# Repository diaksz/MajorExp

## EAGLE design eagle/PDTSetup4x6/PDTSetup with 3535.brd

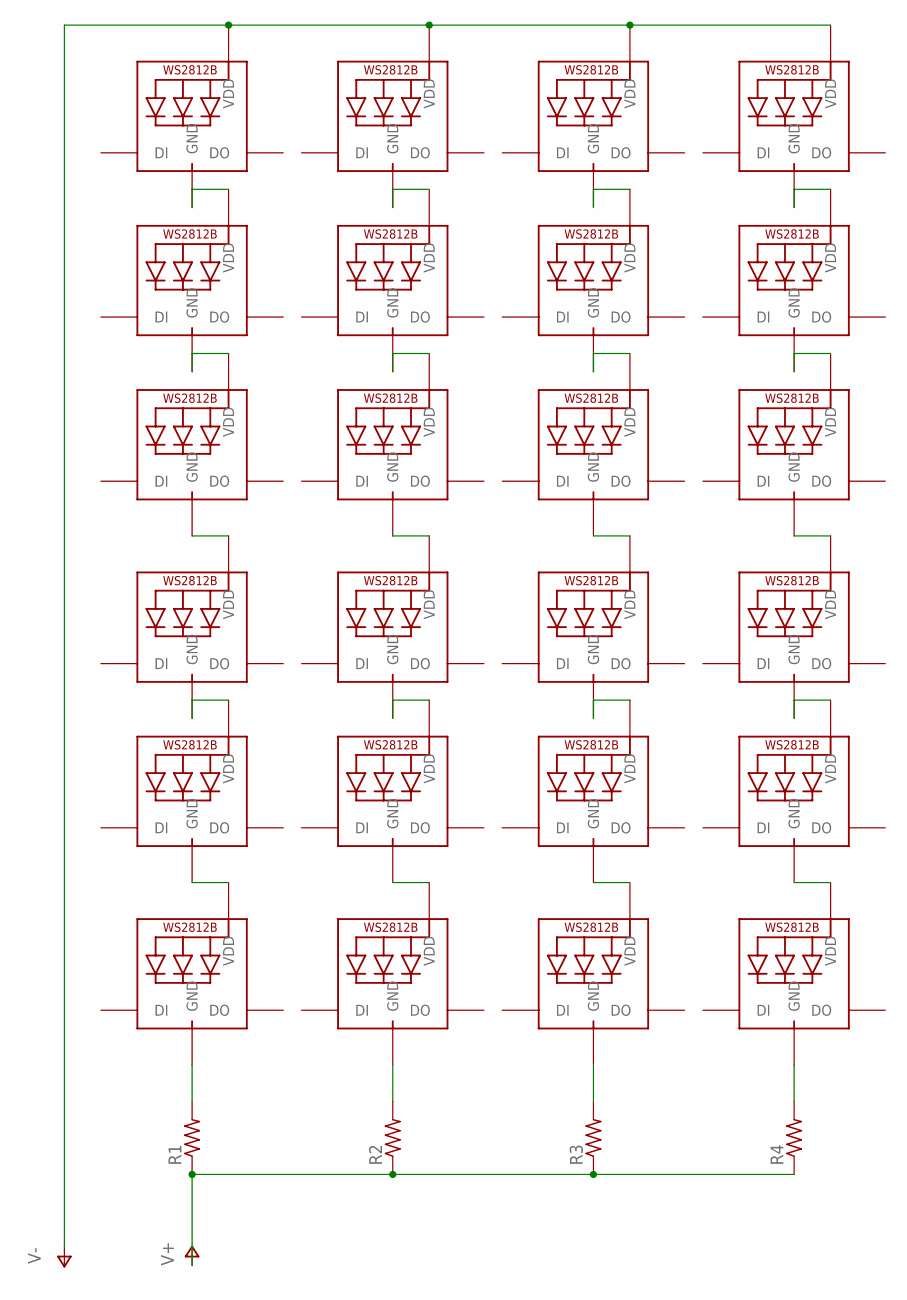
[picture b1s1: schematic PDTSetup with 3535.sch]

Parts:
LED1, LED2, LED3, LED4, LED5, LED6, LED7, LED8, LED9, LED10, LED11, LED12, LED13, LED14, LED15, LED16, LED17, LED18, LED19, LED20, LED21, LED22, LED23, LED24: WS2812B3535; LED3535
R1, R2, R3, R4: R-US_0207/15; 0207/15

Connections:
unnamed: LED24.4 (GND), R4.2
unnamed: LED13.4 (GND), R3.2
unnamed: LED12.4 (GND), R2.2
unnamed: LED6.4 (GND), R1.2
unnamed: LED5.4 (GND), LED6.2 (VDD)
unnamed: LED11.4 (GND), LED12.2 (VDD)
unnamed: LED13.2 (VDD), LED14.4 (GND)
unnamed: LED23.4 (GND), LED24.2 (VDD)
unnamed: LED4.4 (GND), LED5.2 (VDD)
unnamed: LED10.4 (GND), LED11.2 (VDD)
unnamed: LED14.2 (VDD), LED15.4 (GND)
unnamed: LED22.4 (GND), LED23.2 (VDD)
unnamed: LED21.4 (GND), LED22.2 (VDD)
unnamed: LED15.2 (VDD), LED16.4 (GND)
unnamed: LED9.4 (GND), LED10.2 (VDD)
unnamed: LED3.4 (GND), LED4.2 (VDD)
unnamed: LED2.4 (GND), LED3.2 (VDD)
unnamed: LED8.4 (GND), LED9.2 (VDD)
unnamed: LED16.2 (VDD), LED17.4 (GND)
unnamed: LED20.4 (GND), LED21.2 (VDD)
unnamed: LED19.4 (GND), LED20.2 (VDD)
unnamed: LED17.2 (VDD), LED18.4 (GND)
unnamed: LED7.4 (GND), LED8.2 (VDD)
unnamed: LED1.4 (GND), LED2.2 (VDD)
V+: R1.1, R2.1, R3.1, R4.1
V-: LED1.2 (VDD), LED7.2 (VDD), LED18.2 (VDD), LED19.2 (VDD)

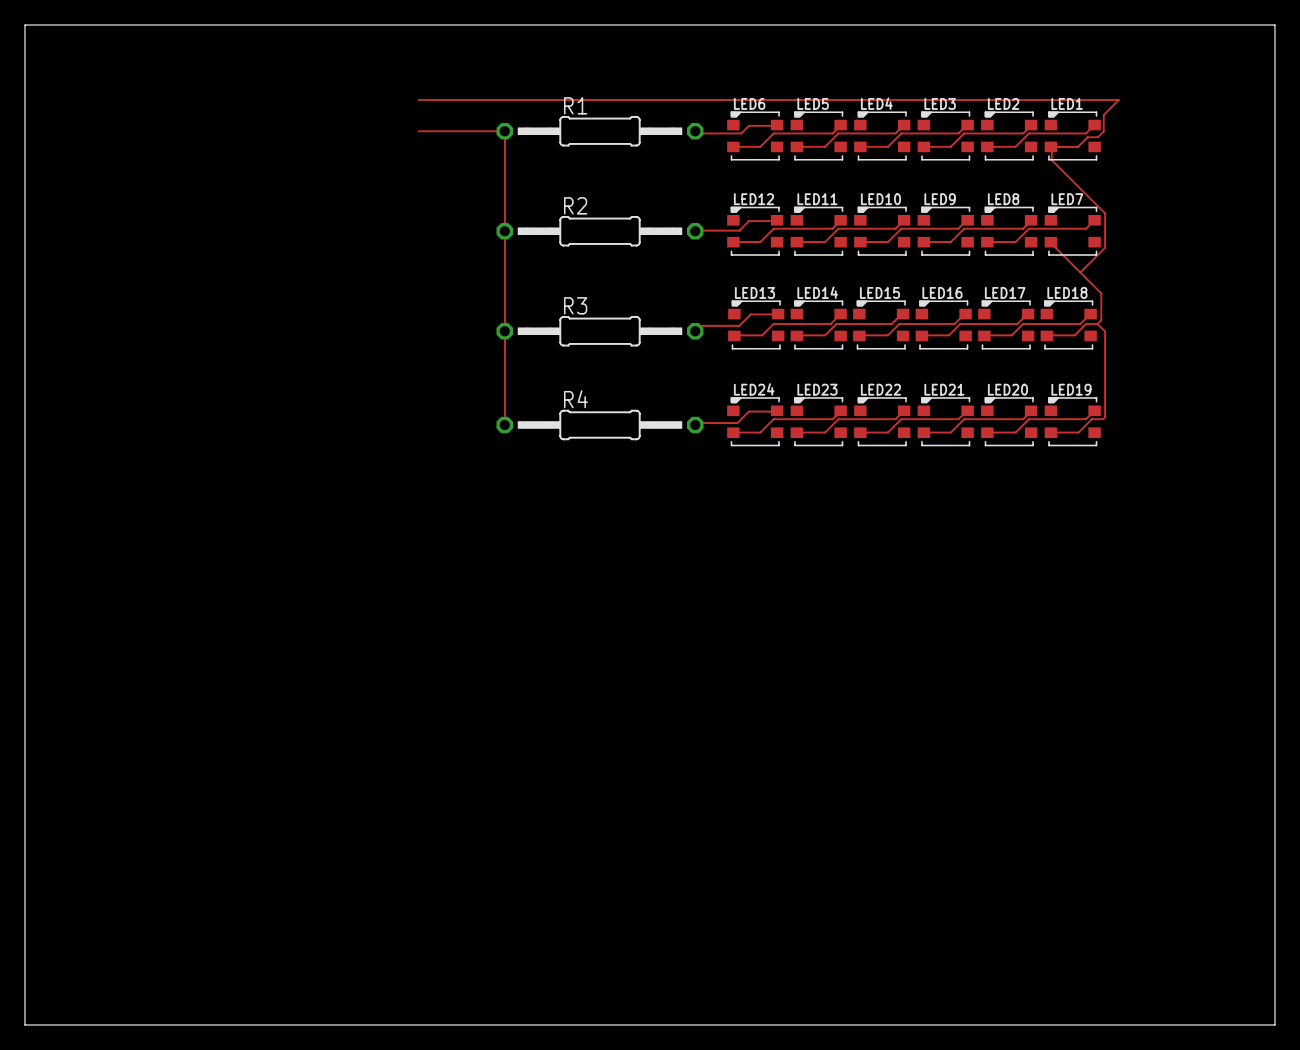
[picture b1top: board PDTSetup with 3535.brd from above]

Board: 2 copper layers, 100.0 x 80.0 mm, 28 parts (0 on the bottom side), 26 nets.

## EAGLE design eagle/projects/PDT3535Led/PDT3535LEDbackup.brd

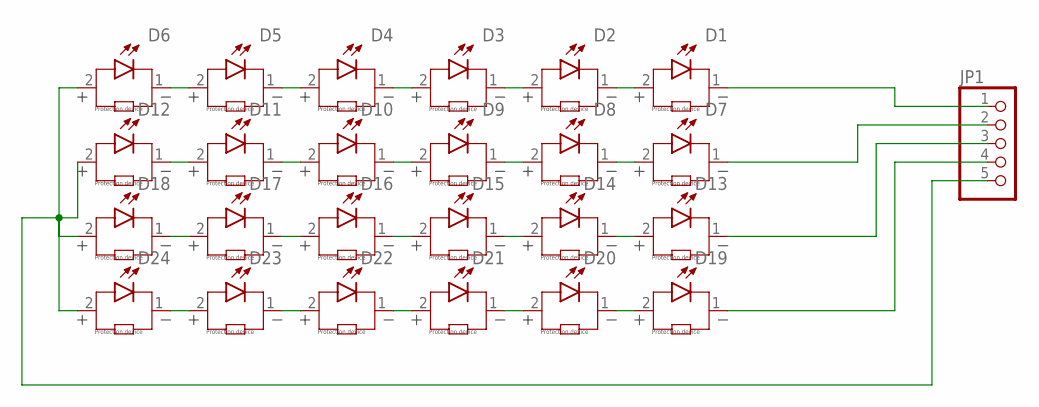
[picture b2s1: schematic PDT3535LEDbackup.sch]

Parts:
D1, D2, D3, D4, D5, D6, D7, D8, D9, D10, D11, D12, D13, D14, D15, D16, D17, D18, D19, D20, D21, D22, D23, D24: WL-SWTC_3535_158353060_6000K; WL-SWTC_3535
JP1: PINHD-1X05_2.54-SMD-90°; 1X05SMD/90

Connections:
unnamed: D6.2, D12.2, D18.2, D24.2, JP1.5
unnamed: D5.2, D6.1
unnamed: D4.2, D5.1
unnamed: D3.2, D4.1
unnamed: D2.2, D3.1
unnamed: D1.2, D2.1
unnamed: D11.2, D12.1
unnamed: D17.2, D18.1
unnamed: D23.2, D24.1
unnamed: D22.2, D23.1
unnamed: D16.2, D17.1
unnamed: D10.2, D11.1
unnamed: D9.2, D10.1
unnamed: D15.2, D16.1
unnamed: D21.2, D22.1
unnamed: D20.2, D21.1
unnamed: D14.2, D15.1
unnamed: D8.2, D9.1
unnamed: D7.2, D8.1
unnamed: D13.2, D14.1
unnamed: D19.2, D20.1
unnamed: D19.1, JP1.4
unnamed: D13.1, JP1.3
unnamed: D7.1, JP1.2
unnamed: D1.1, JP1.1

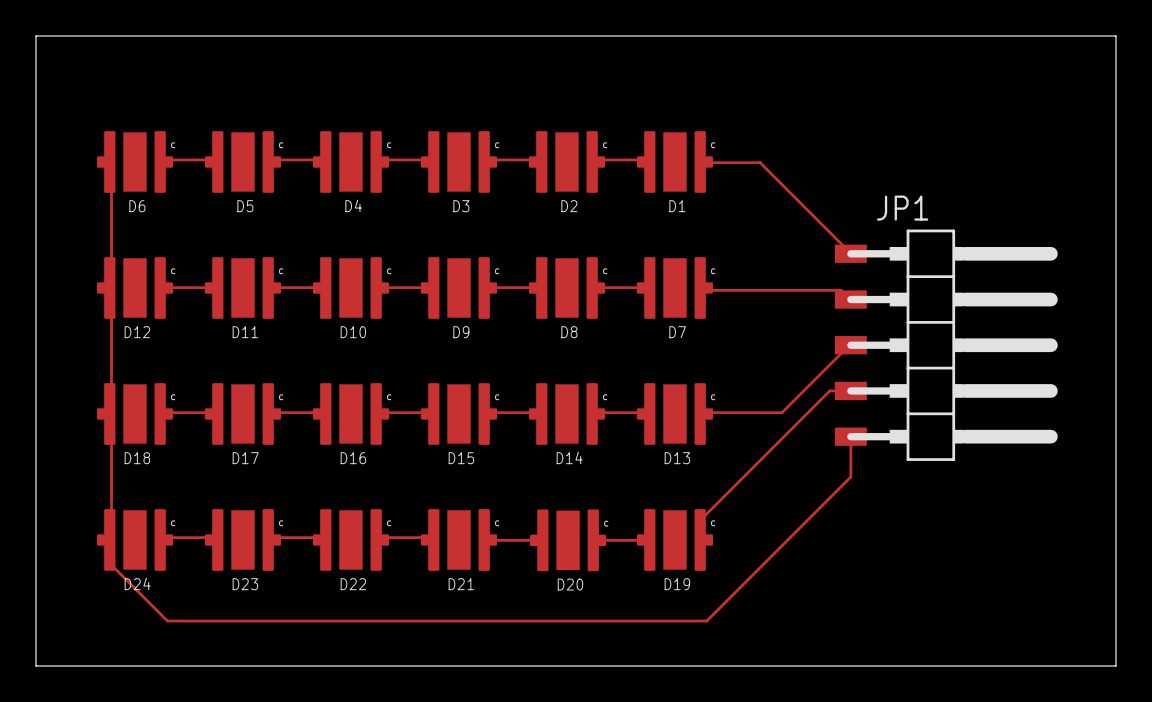
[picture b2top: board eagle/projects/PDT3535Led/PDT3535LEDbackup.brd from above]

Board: 2 copper layers, 60.0 x 35.0 mm, 25 parts (0 on the bottom side), 25 nets.

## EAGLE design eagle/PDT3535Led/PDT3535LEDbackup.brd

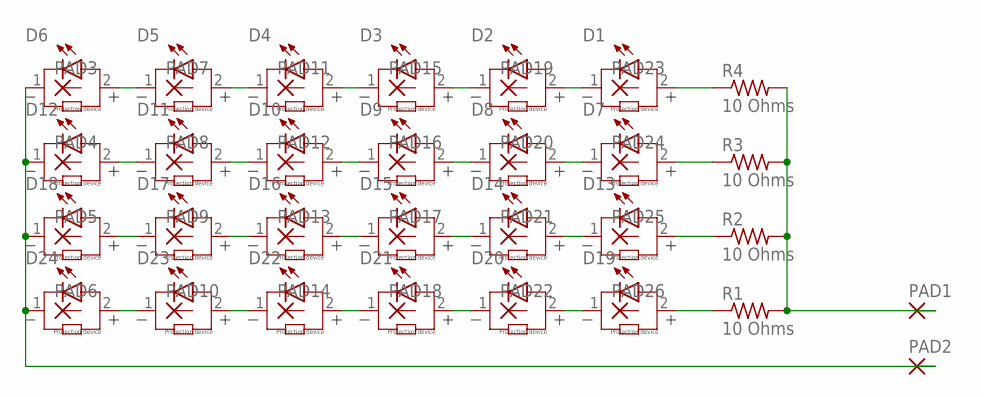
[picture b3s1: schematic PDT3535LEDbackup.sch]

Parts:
D1, D2, D3, D4, D5, D6, D7, D8, D9, D10, D11, D12, D13, D14, D15, D16, D17, D18, D19, D20, D21, D22, D23, D24: WL-SWTC_3535_158353060_6000K; WL-SWTC_3535
PAD1, PAD2: 1,6/0,8
PAD3, PAD4, PAD5, PAD6, PAD7, PAD8, PAD9, PAD10, PAD11, PAD12, PAD13, PAD14, PAD15, PAD16, PAD17, PAD18, PAD19, PAD20, PAD21, PAD22, PAD23, PAD24, PAD25, PAD26: 2,54/1,1
R1, R2, R3, R4: 10 Ohms; 0617/22

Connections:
unnamed: D19.2, R1.1
unnamed: D19.1, D20.2
unnamed: D20.1, D21.2
unnamed: D21.1, D22.2
unnamed: D22.1, D23.2
unnamed: D23.1, D24.2
unnamed: D13.2, R2.1
unnamed: D13.1, D14.2
unnamed: D14.1, D15.2
unnamed: D15.1, D16.2
unnamed: D16.1, D17.2
unnamed: D17.1, D18.2
unnamed: D7.2, R3.1
unnamed: D7.1, D8.2
unnamed: D8.1, D9.2
unnamed: D9.1, D10.2
unnamed: D10.1, D11.2
unnamed: D11.1, D12.2
unnamed: D1.2, R4.1
unnamed: D1.1, D2.2
unnamed: D2.1, D3.2
unnamed: D3.1, D4.2
unnamed: D4.1, D5.2
unnamed: D5.1, D6.2
unnamed: D6.1, D12.1, D18.1, D24.1, PAD2.1
unnamed: PAD1.1, R1.2, R2.2, R3.2, R4.2

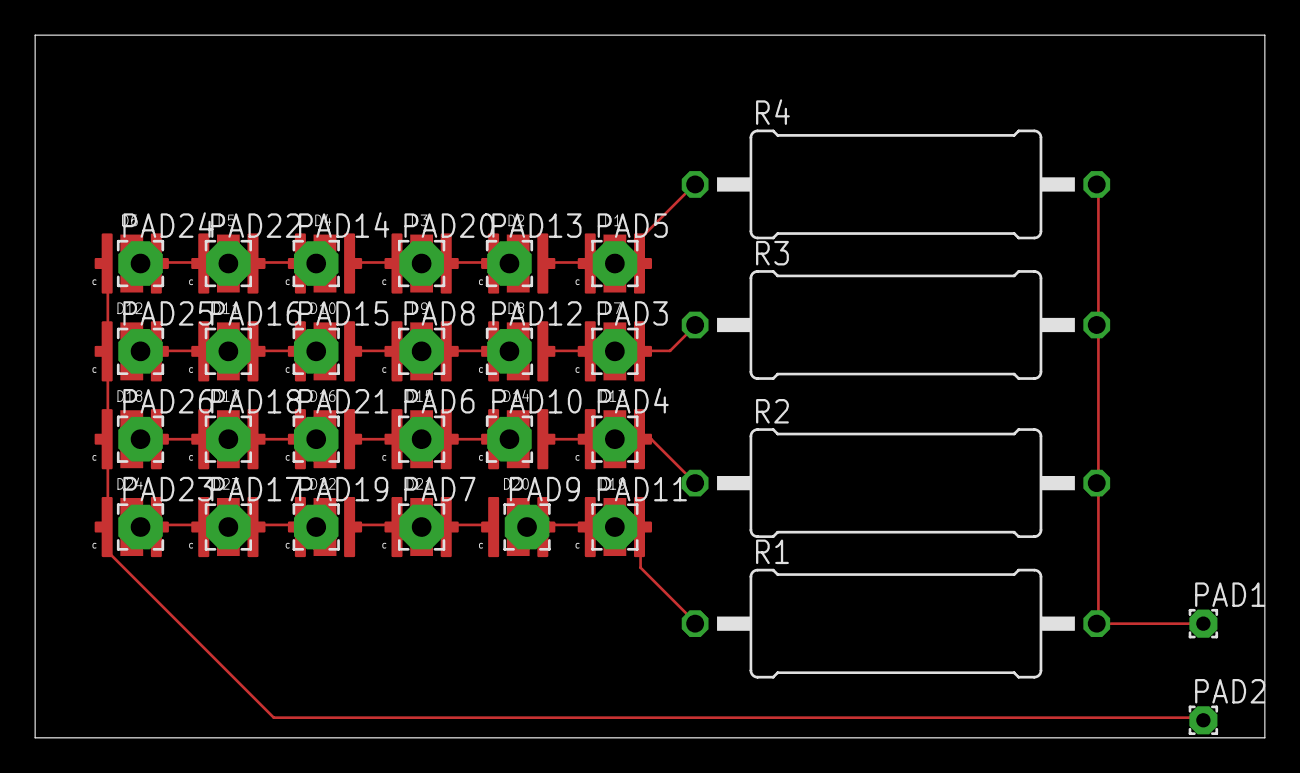
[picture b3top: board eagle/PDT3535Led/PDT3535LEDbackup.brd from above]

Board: 2 copper layers, 70.0 x 40.0 mm, 54 parts (0 on the bottom side), 26 nets.

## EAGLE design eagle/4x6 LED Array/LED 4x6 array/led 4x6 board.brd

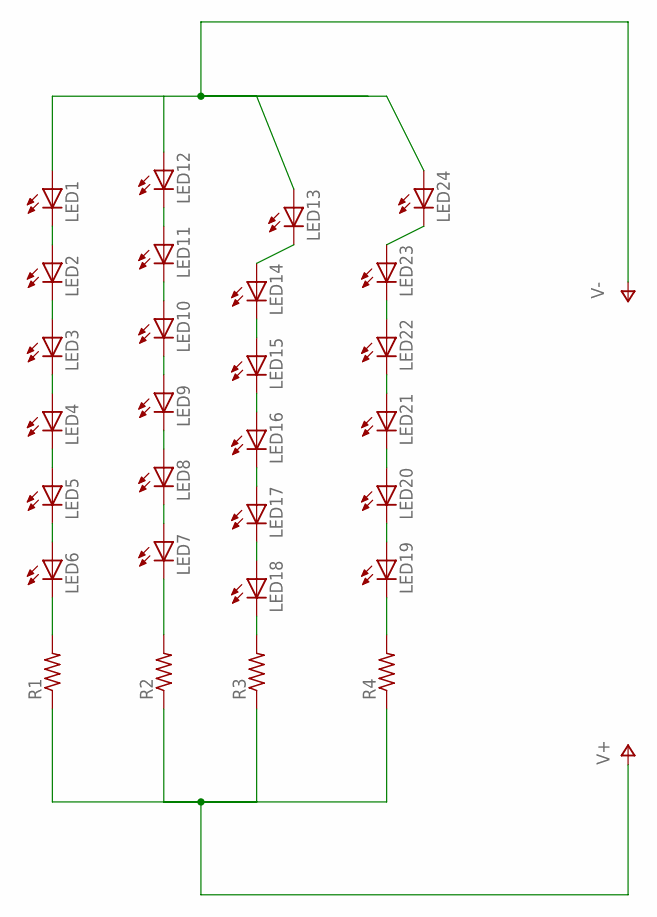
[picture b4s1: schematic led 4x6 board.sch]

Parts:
LED1, LED2, LED3, LED4, LED5, LED6, LED7, LED8, LED9, LED10, LED11, LED12, LED13, LED14, LED15, LED16, LED17, LED18, LED19, LED20, LED21, LED22, LED23, LED24: LEDLZR181; LZR181
R1, R2, R3, R4: R-US_V234/12; V234/12

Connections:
unnamed: LED9.A, LED10.K (C)
unnamed: LED22.A, LED23.K (C)
unnamed: LED13.K (C), LED14.A
unnamed: LED14.K (C), LED15.A
unnamed: LED15.K (C), LED16.A
unnamed: LED16.K (C), LED17.A
unnamed: LED17.K (C), LED18.A
unnamed: LED1.K (C), LED2.A
unnamed: LED2.K (C), LED3.A
unnamed: LED3.K (C), LED4.A
unnamed: LED4.K (C), LED5.A
unnamed: LED8.A, LED9.K (C)
unnamed: LED7.A, LED8.K (C)
unnamed: LED11.A, LED12.K (C)
unnamed: LED5.K (C), LED6.A
unnamed: LED6.K (C), R1.2
unnamed: LED10.A, LED11.K (C)
unnamed: LED7.K (C), R2.2
unnamed: LED18.K (C), R3.2
unnamed: LED23.A, LED24.K (C)
unnamed: LED21.A, LED22.K (C)
unnamed: LED20.A, LED21.K (C)
unnamed: LED19.A, LED20.K (C)
unnamed: LED19.K (C), R4.2
V+: R1.1, R2.1, R3.1, R4.1
V-: LED1.A, LED12.A, LED13.A, LED24.A

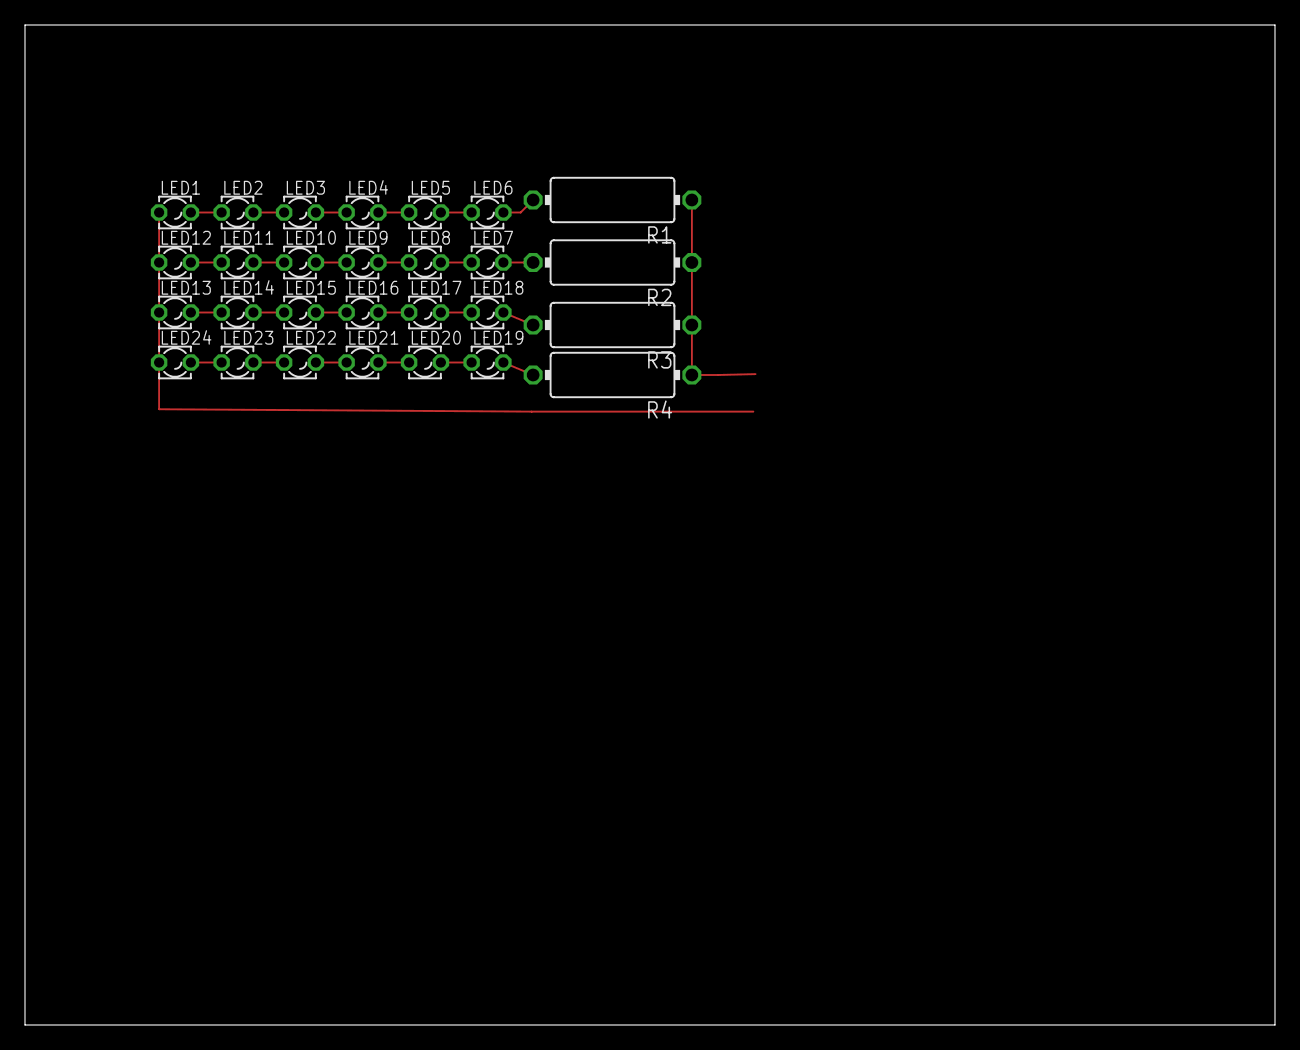
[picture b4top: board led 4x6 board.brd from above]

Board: 2 copper layers, 100.0 x 80.0 mm, 28 parts (0 on the bottom side), 26 nets.

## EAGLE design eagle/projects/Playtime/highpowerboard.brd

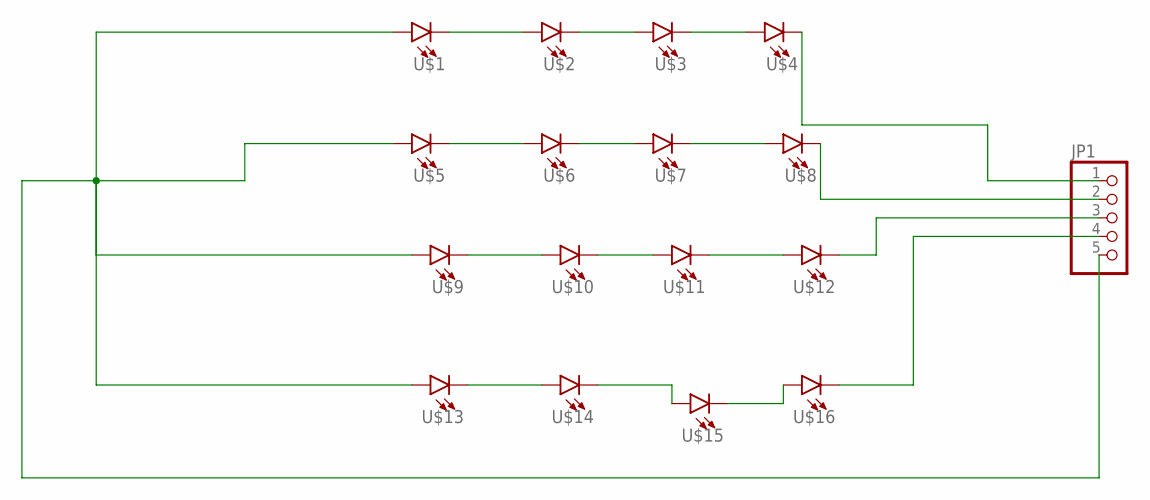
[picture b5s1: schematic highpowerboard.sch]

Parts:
JP1: PINHD-1X05_2.54-SMD-90°; 1X05SMD/90
U$1, U$2, U$3, U$4, U$5, U$6, U$7, U$8, U$9, U$10, U$11, U$12, U$13, U$14, U$15, U$16: LEDHIGHPOWER; HIGHPOWERLED

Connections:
unnamed: U$1.PI$ (C), U$2.PO$ (A)
unnamed: U$2.PI$ (C), U$3.PO$ (A)
unnamed: U$3.PI$ (C), U$4.PO$ (A)
unnamed: JP1.1, U$4.PI$ (C)
unnamed: U$5.PI$ (C), U$6.PO$ (A)
unnamed: U$6.PI$ (C), U$7.PO$ (A)
unnamed: U$7.PI$ (C), U$8.PO$ (A)
unnamed: JP1.2, U$8.PI$ (C)
unnamed: U$9.PI$ (C), U$10.PO$ (A)
unnamed: U$10.PI$ (C), U$11.PO$ (A)
unnamed: U$11.PI$ (C), U$12.PO$ (A)
unnamed: JP1.3, U$12.PI$ (C)
unnamed: U$13.PI$ (C), U$14.PO$ (A)
unnamed: U$14.PI$ (C), U$15.PO$ (A)
unnamed: U$15.PI$ (C), U$16.PO$ (A)
unnamed: JP1.4, U$16.PI$ (C)
unnamed: JP1.5, U$1.PO$ (A), U$5.PO$ (A), U$9.PO$ (A), U$13.PO$ (A)

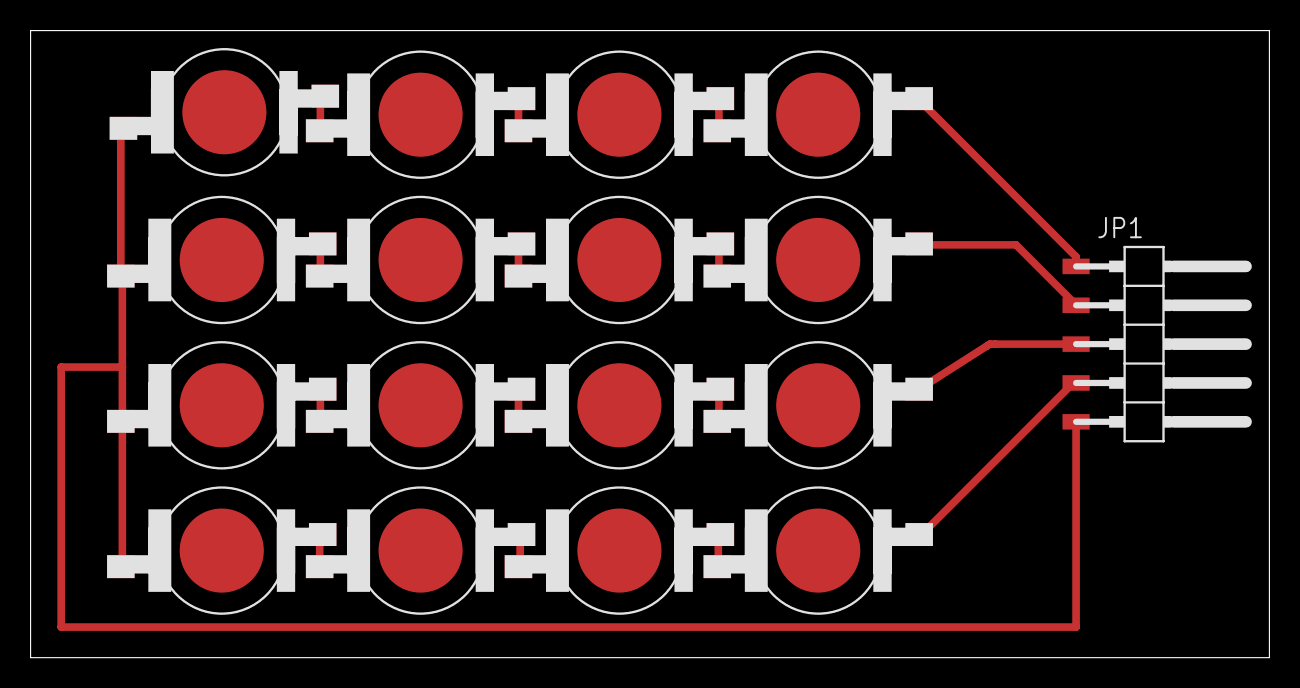
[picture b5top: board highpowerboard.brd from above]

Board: 2 copper layers, 81.0 x 41.0 mm, 17 parts (0 on the bottom side), 17 nets.

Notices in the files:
parts and their libraries:
Wurth_Elektronik_Optoelectronics_rev17b: Copyright: Würth Elektronik
